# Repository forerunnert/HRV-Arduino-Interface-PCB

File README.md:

# HRV-Arduino-Interface-PCB
circuit board design for HRV Arduino interface

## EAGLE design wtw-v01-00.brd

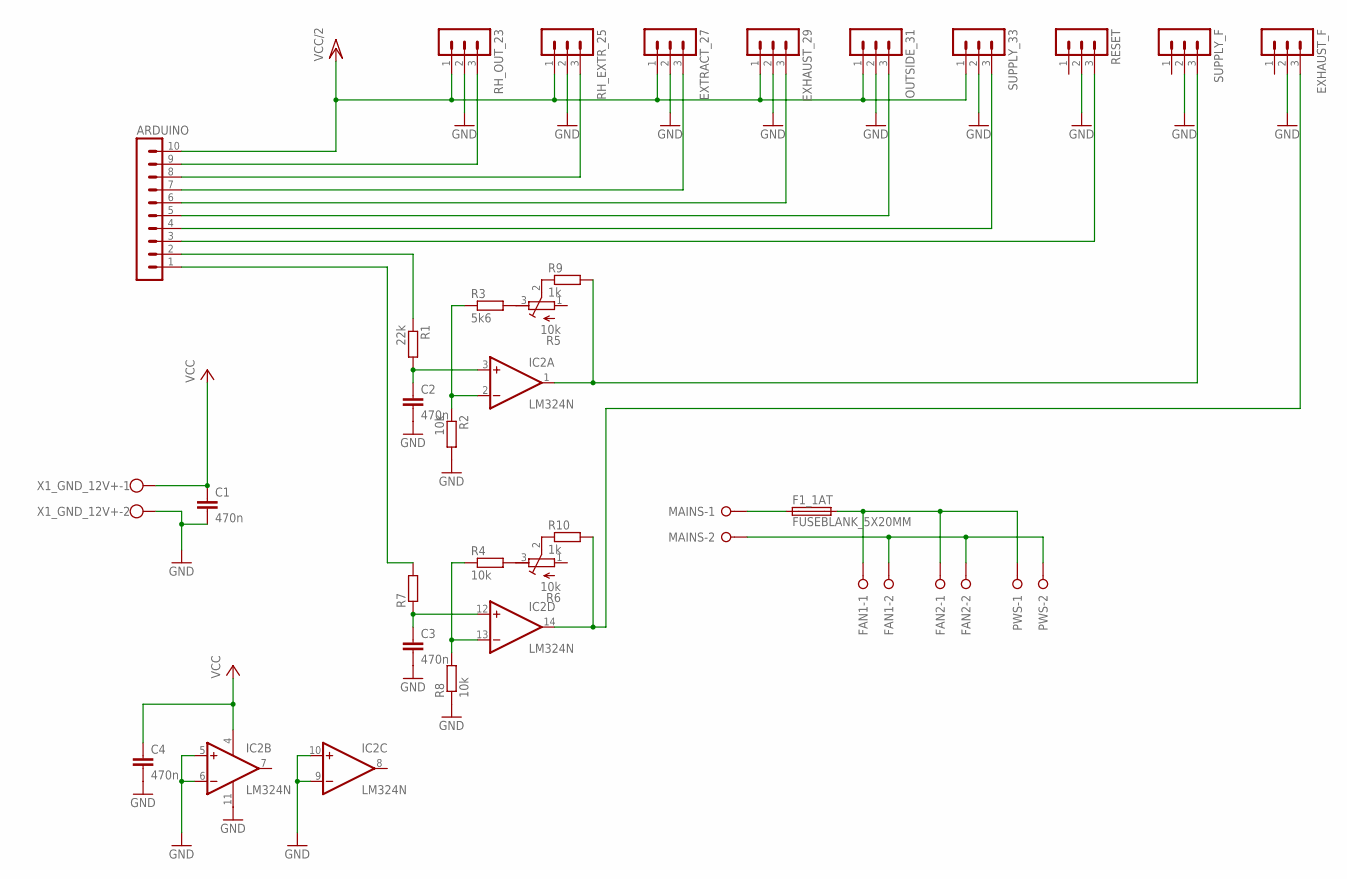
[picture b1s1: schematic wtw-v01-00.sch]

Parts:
ARDUINO: MA10-1
C1, C2, C3, C4: 470n; C050-030X075
EXHAUST_29: MA03-1
EXHAUST_F: MA03-1
EXTRACT_27: MA03-1
F1_1AT: FUSEBLANK_5X20MM; FUSE_HOLDER_5X20MM
FAN1, FAN2: W237-02P; W237-132
IC2: LM324N; DIL14
MAINS: W237-02P; W237-132
OUTSIDE_31: MA03-1
PWS: W237-02P; W237-132
R1: 22k; V234/12
R2, R4, R8: 10k; V234/12
R3: 5k6; V234/12
R5, R6: 10k; RTRIM64W
R7: R-EU_V234/12; V234/12
R9, R10: 1k; V234/12
RESET: MA03-1
RH_EXTR_25: MA03-1
RH_OUT_23: MA03-1
SUPPLY_33: MA03-1
SUPPLY_F: MA03-1
X1_GND_12V+: W237-4

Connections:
GND: C1.2, C2.2, C3.2, C4.2, EXHAUST_29.2, EXHAUST_F.2, EXTRACT_27.2, IC2.5 (+IN), IC2.6 (-IN), IC2.9 (-IN), IC2.10 (+IN), IC2.11 (V-), OUTSIDE_31.2, R2.2, R8.1, RESET.2, RH_EXTR_25.2, RH_OUT_23.2, SUPPLY_33.2, SUPPLY_F.2, X1_GND_12V+.2
unnamed: R3.2, R5.3 (E)
unnamed: R4.2, R6.3 (E)
unnamed: ARDUINO.2, R1.1
unnamed: ARDUINO.1, R7.2
unnamed: C2.1, IC2.3 (+IN), R1.2
unnamed: C3.1, IC2.12 (+IN), R7.1
unnamed: IC2.2 (-IN), R2.1, R3.1
unnamed: IC2.13 (-IN), R4.1, R8.2
unnamed: ARDUINO.9, RH_OUT_23.3
unnamed: ARDUINO.8, RH_EXTR_25.3
unnamed: ARDUINO.7, EXTRACT_27.3
unnamed: ARDUINO.6, EXHAUST_29.3
unnamed: ARDUINO.5, OUTSIDE_31.3
unnamed: ARDUINO.4, SUPPLY_33.3
unnamed: ARDUINO.3, RESET.3
unnamed: IC2.1 (OUT), R9.2, SUPPLY_F.3
unnamed: EXHAUST_F.3, IC2.14 (OUT), R10.2
unnamed: R5.2 (S), R9.1
unnamed: R6.2 (S), R10.1
unnamed: F1_1AT.1, MAINS.1
unnamed: F1_1AT.2, FAN1.1, FAN2.1, PWS.1
unnamed: FAN1.2, FAN2.2, MAINS.2, PWS.2
VCC: C1.1, C4.1, IC2.4 (V+), X1_GND_12V+.1
VCC/2: ARDUINO.10, EXHAUST_29.1, EXTRACT_27.1, OUTSIDE_31.1, RH_EXTR_25.1, RH_OUT_23.1, SUPPLY_33.1

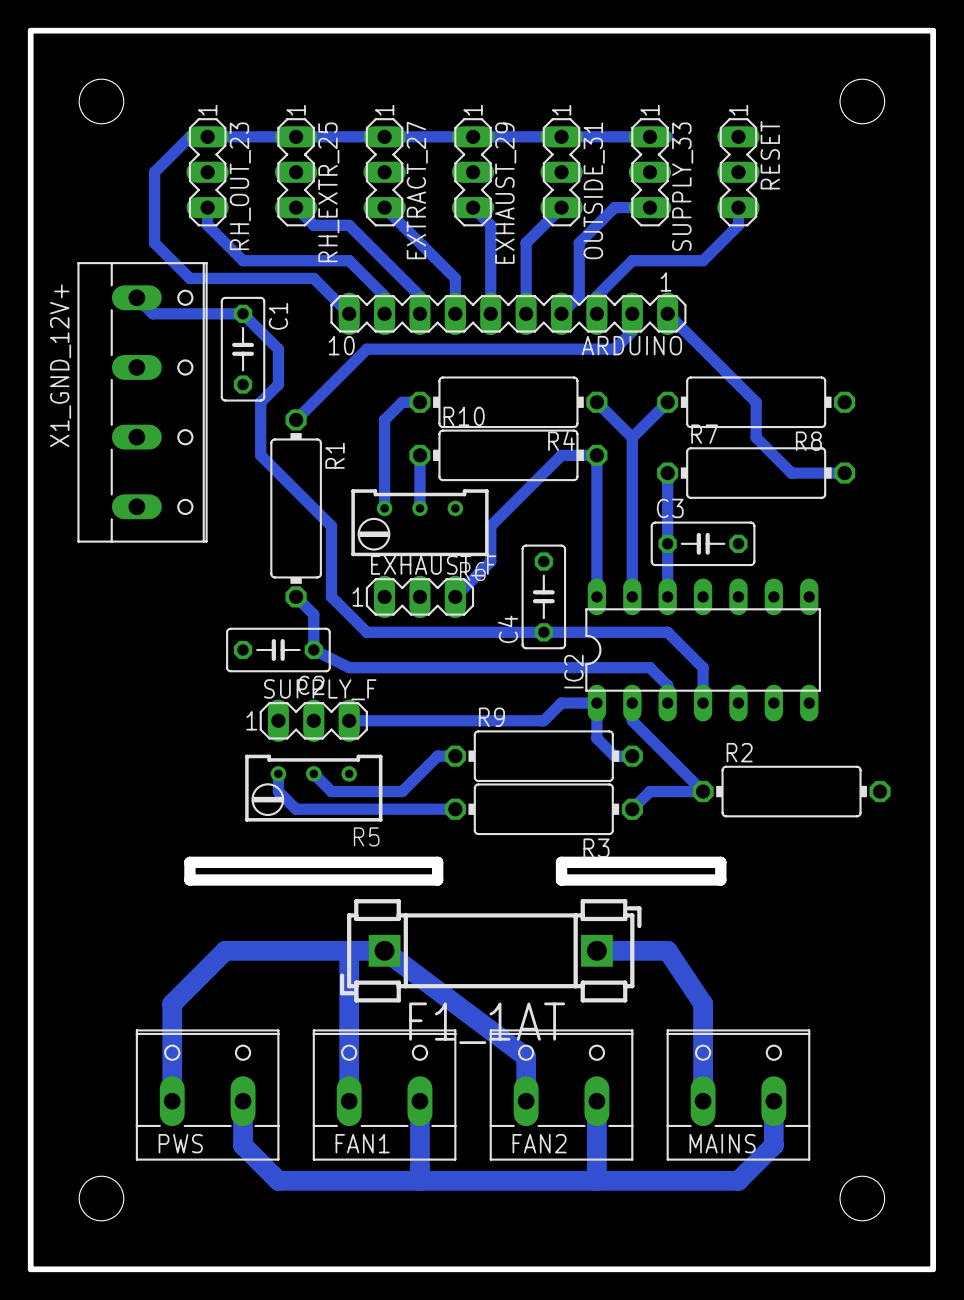
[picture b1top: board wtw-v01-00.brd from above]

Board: 2 copper layers, 64.4 x 88.5 mm, 31 parts (0 on the bottom side), 25 nets.

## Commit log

2017-03-29 Added board screenshots
